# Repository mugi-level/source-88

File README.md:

# source-88
アナログなFMラジオ

https://www.youtube.com/watch?v=PpNnA6v0uf0

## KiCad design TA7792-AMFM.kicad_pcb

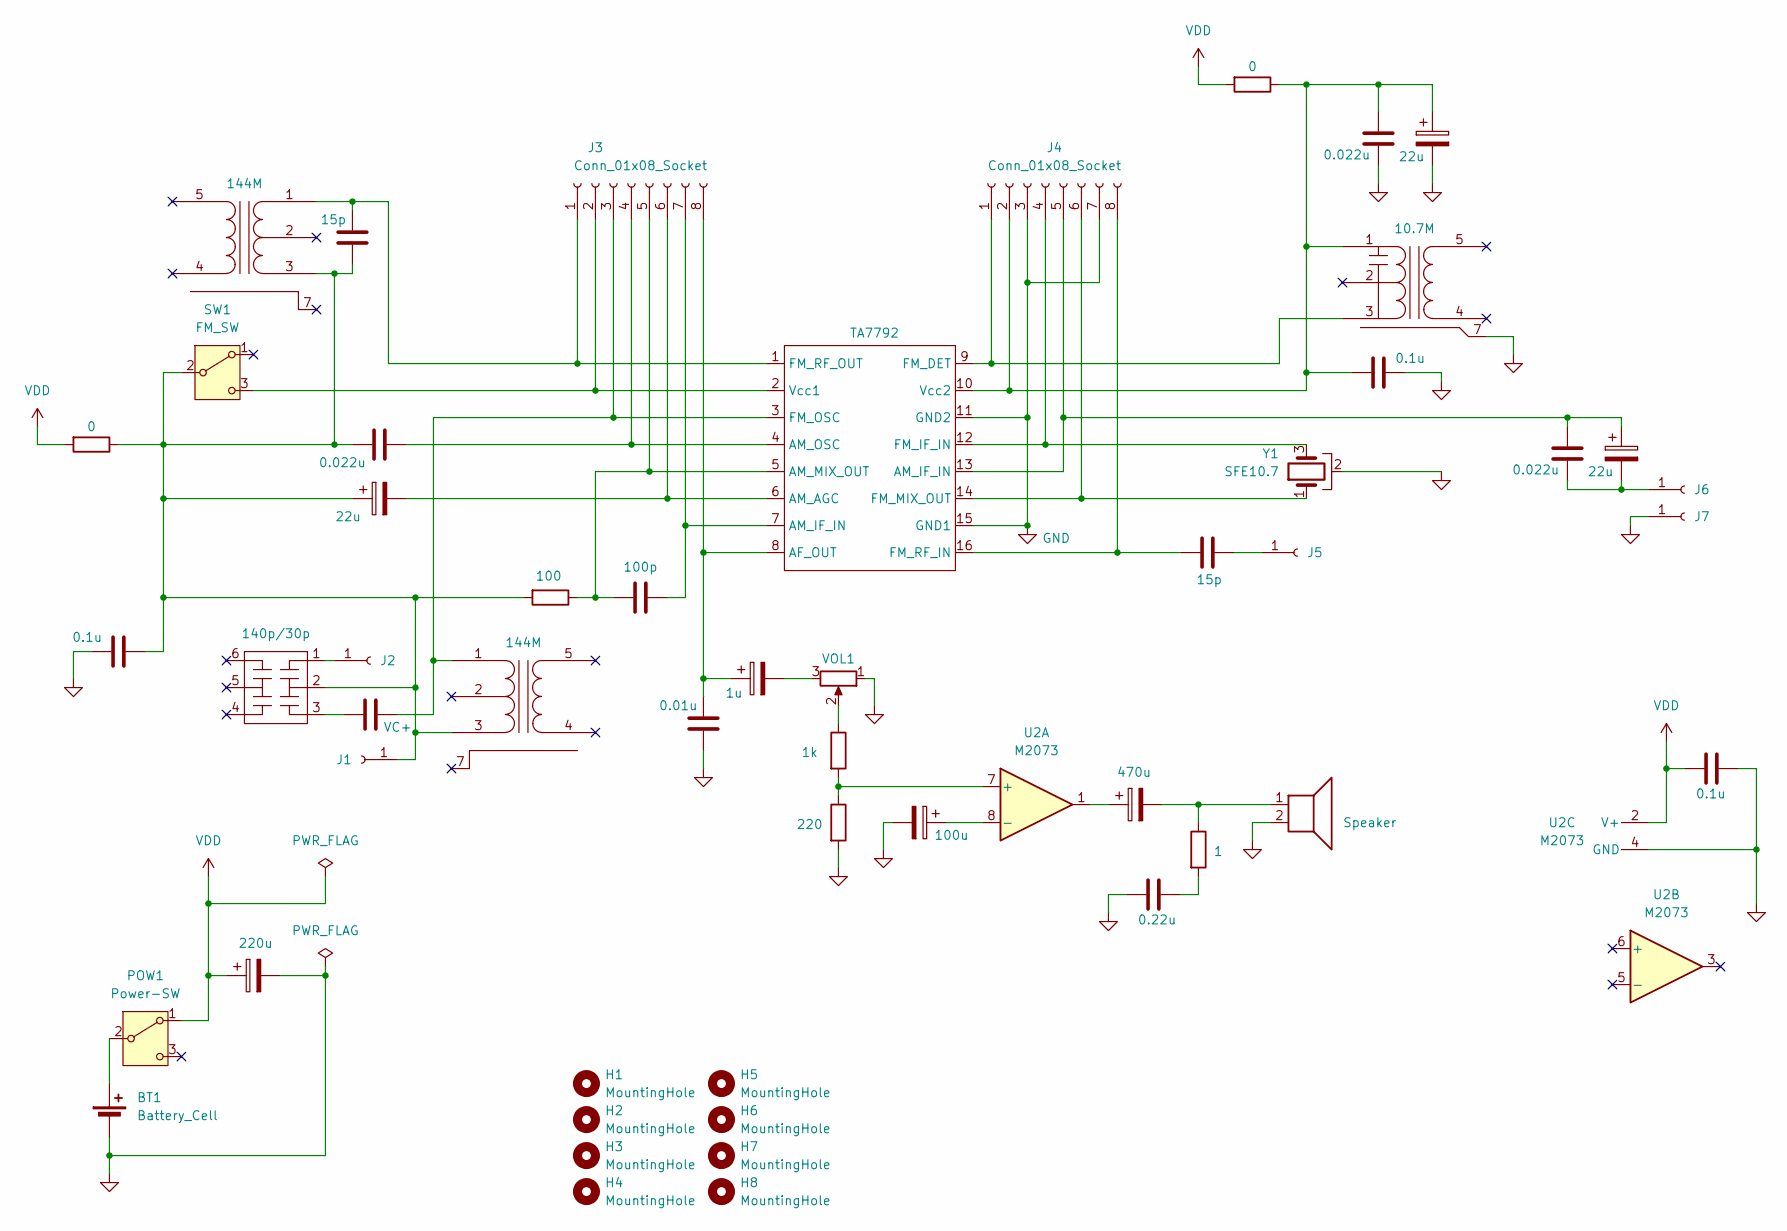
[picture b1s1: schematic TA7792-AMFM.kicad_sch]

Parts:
BT1: Battery_Cell; JST_PH_B2B-PH-K_1x02_P2.00mm_Vertical
C1, C15, C19: 0.1u; C_Disc_D3.8mm_W2.6mm_P2.50mm
C2: 220u; CP_Radial_D6.3mm_P2.50mm
C3, C13: 15p; C_Disc_D3.0mm_W1.6mm_P2.50mm
C4: VC+; C_Disc_D3.0mm_W1.6mm_P2.50mm
C5, C14, C17: 0.022u; C_Disc_D7.0mm_W2.5mm_P5.00mm
C6, C16, C18: 22u; CP_Radial_D5.0mm_P2.00mm
C7: 100p; C_Disc_D3.0mm_W1.6mm_P2.50mm
C8: 0.01u; C_Disc_D7.0mm_W2.5mm_P5.00mm
C9: 1u; CP_Radial_D5.0mm_P2.00mm
C10: 100u; CP_Radial_D5.0mm_P2.00mm
C11: 470u; CP_Radial_D8.0mm_P3.50mm
C12: 0.22u; C_Disc_D7.0mm_W2.5mm_P5.00mm
H1, H2, H3, H4, H5, H6, H7, H8: MountingHole; MountingHole_3.2mm_M3
J1: AM-ANTV; PinHeader_1x01_P2.54mm_Vertical
J2: AM-ANT; PinHeader_1x01_P2.54mm_Vertical
J3, J4: Conn_01x08_Socket; PinSocket_1x08_P2.54mm_Vertical
J5: FM-ANT; PinHeader_1x01_P2.54mm_Vertical
J6: AM-IF; PinHeader_1x01_P2.54mm_Vertical
J7: AM-IFG; PinHeader_1x01_P2.54mm_Vertical
POW1: Power-SW; JST_PH_B3B-PH-K_1x03_P2.00mm_Vertical
R1, R6: 0; R_Axial_DIN0207_L6.3mm_D2.5mm_P7.62mm_Horizontal
R2: 100; R_Axial_DIN0207_L6.3mm_D2.5mm_P7.62mm_Horizontal
R3: 1k; R_Axial_DIN0207_L6.3mm_D2.5mm_P7.62mm_Horizontal
R4: 220; R_Axial_DIN0207_L6.3mm_D2.5mm_P7.62mm_Horizontal
R5: 1; R_Axial_DIN0207_L6.3mm_D2.5mm_P7.62mm_Horizontal
SP1: Speaker; JST_PH_B2B-PH-K_1x02_P2.00mm_Vertical
SW1: FM_SW; JST_PH_B3B-PH-K_1x03_P2.00mm_Vertical
T1, T2: 144M; FCZ-10S
T3: 10.7M; FCZ-10S
U1: TA7792; TA7792F
U2: M2073; DIP-8_W7.62mm_LongPads
VC1: 140p/30p; VC-HW443
VOL1: R_Potentiometer; JST_PH_B3B-PH-K_1x03_P2.00mm_Vertical
Y1: SFE10.7

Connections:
GND: BT1.2 (-), C1.2, C2.2, C8.2, C10.2, C12.2, C14.2, C15.1, C16.2, C19.1, J4.3, J4.7, J7.1, R4.2, SP1.2, T3.7 (G), U1.11 (GND2), U1.15 (GND1), U2.4 (GND), VOL1.1, Y1.2
unnamed: BT1.1 (+), POW1.2 (B)
unnamed: C4.2, VC1.3
unnamed: C9.2, VOL1.3
unnamed: C11.1, U2.1
unnamed: C11.2, R5.1, SP1.1
unnamed: C12.1, R5.2
unnamed: C1.1, C3.2, C5.2, C6.1, J1.1, R1.1, R2.2, SW1.2 (B), T1.3 (PR2), T2.3 (PR2), VC1.2
unnamed: J2.1, VC1.1
unnamed: C3.1, J3.1, T1.1 (PR1), U1.1 (FM_RF_OUT)
unnamed: J3.2, SW1.3 (C), U1.2 (Vcc1)
unnamed: C4.1, J3.3, T2.1 (PR1), U1.3 (FM_OSC)
unnamed: C5.1, J3.4, U1.4 (AM_OSC)
unnamed: C7.1, J3.5, R2.1, U1.5 (AM_MIX_OUT)
unnamed: C6.2, J3.6, U1.6 (AM_AGC)
unnamed: C7.2, J3.7, U1.7 (AM_IF_IN)
unnamed: C8.1, C9.1, J3.8, U1.8 (AF_OUT)
unnamed: J4.1, T3.3 (PR2), U1.9 (FM_DET)
unnamed: C14.1, C15.2, C16.1, J4.2, R6.1, T3.1 (PR1), U1.10 (Vcc2)
unnamed: J4.4, U1.12 (FM_IF_IN), Y1.3
unnamed: C17.1, C18.1, J4.5, U1.13 (AM_IF_IN)
unnamed: J4.6, U1.14 (FM_MIX_OUT), Y1.1
unnamed: C13.2, J4.8, U1.16 (FM_RF_IN)
unnamed: C13.1, J5.1
unnamed: C17.2, C18.2, J6.1
unnamed: R3.1, VOL1.2
unnamed: R3.2, R4.1, U2.7 (+)
unnamed: C10.1, U2.8 (-)
VDD: C2.1, C19.2, POW1.1 (A), R1.2, R6.2, U2.2 (V+)

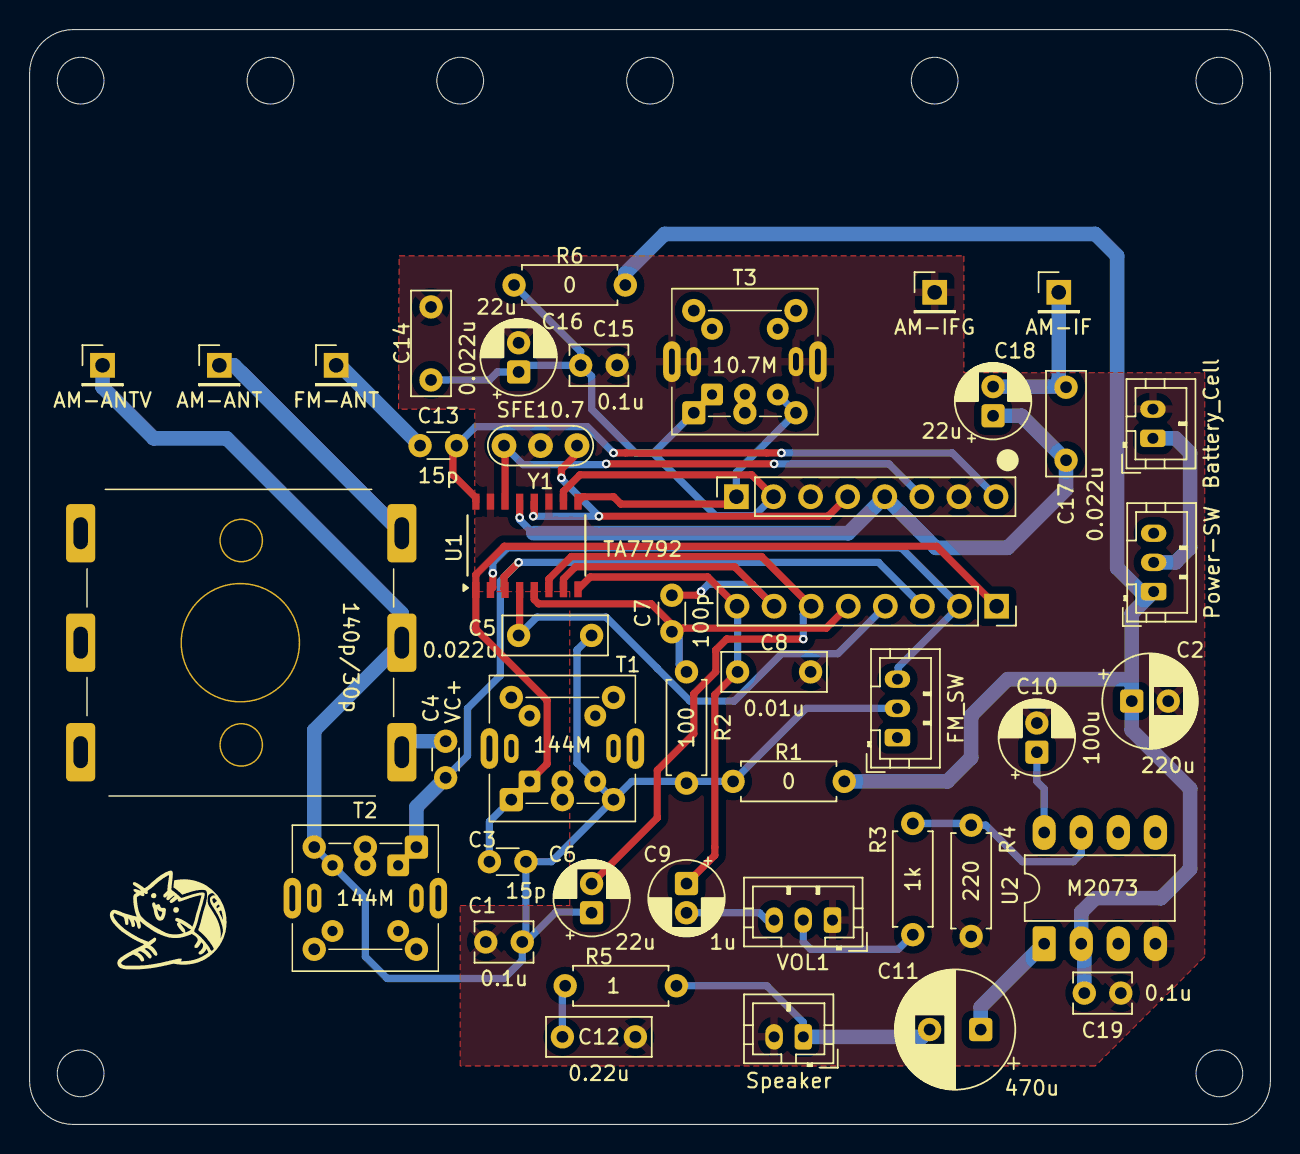
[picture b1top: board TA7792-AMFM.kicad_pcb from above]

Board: 2 copper layers, 85.0 x 75.0 mm, 52 parts (0 on the bottom side), 29 nets.
